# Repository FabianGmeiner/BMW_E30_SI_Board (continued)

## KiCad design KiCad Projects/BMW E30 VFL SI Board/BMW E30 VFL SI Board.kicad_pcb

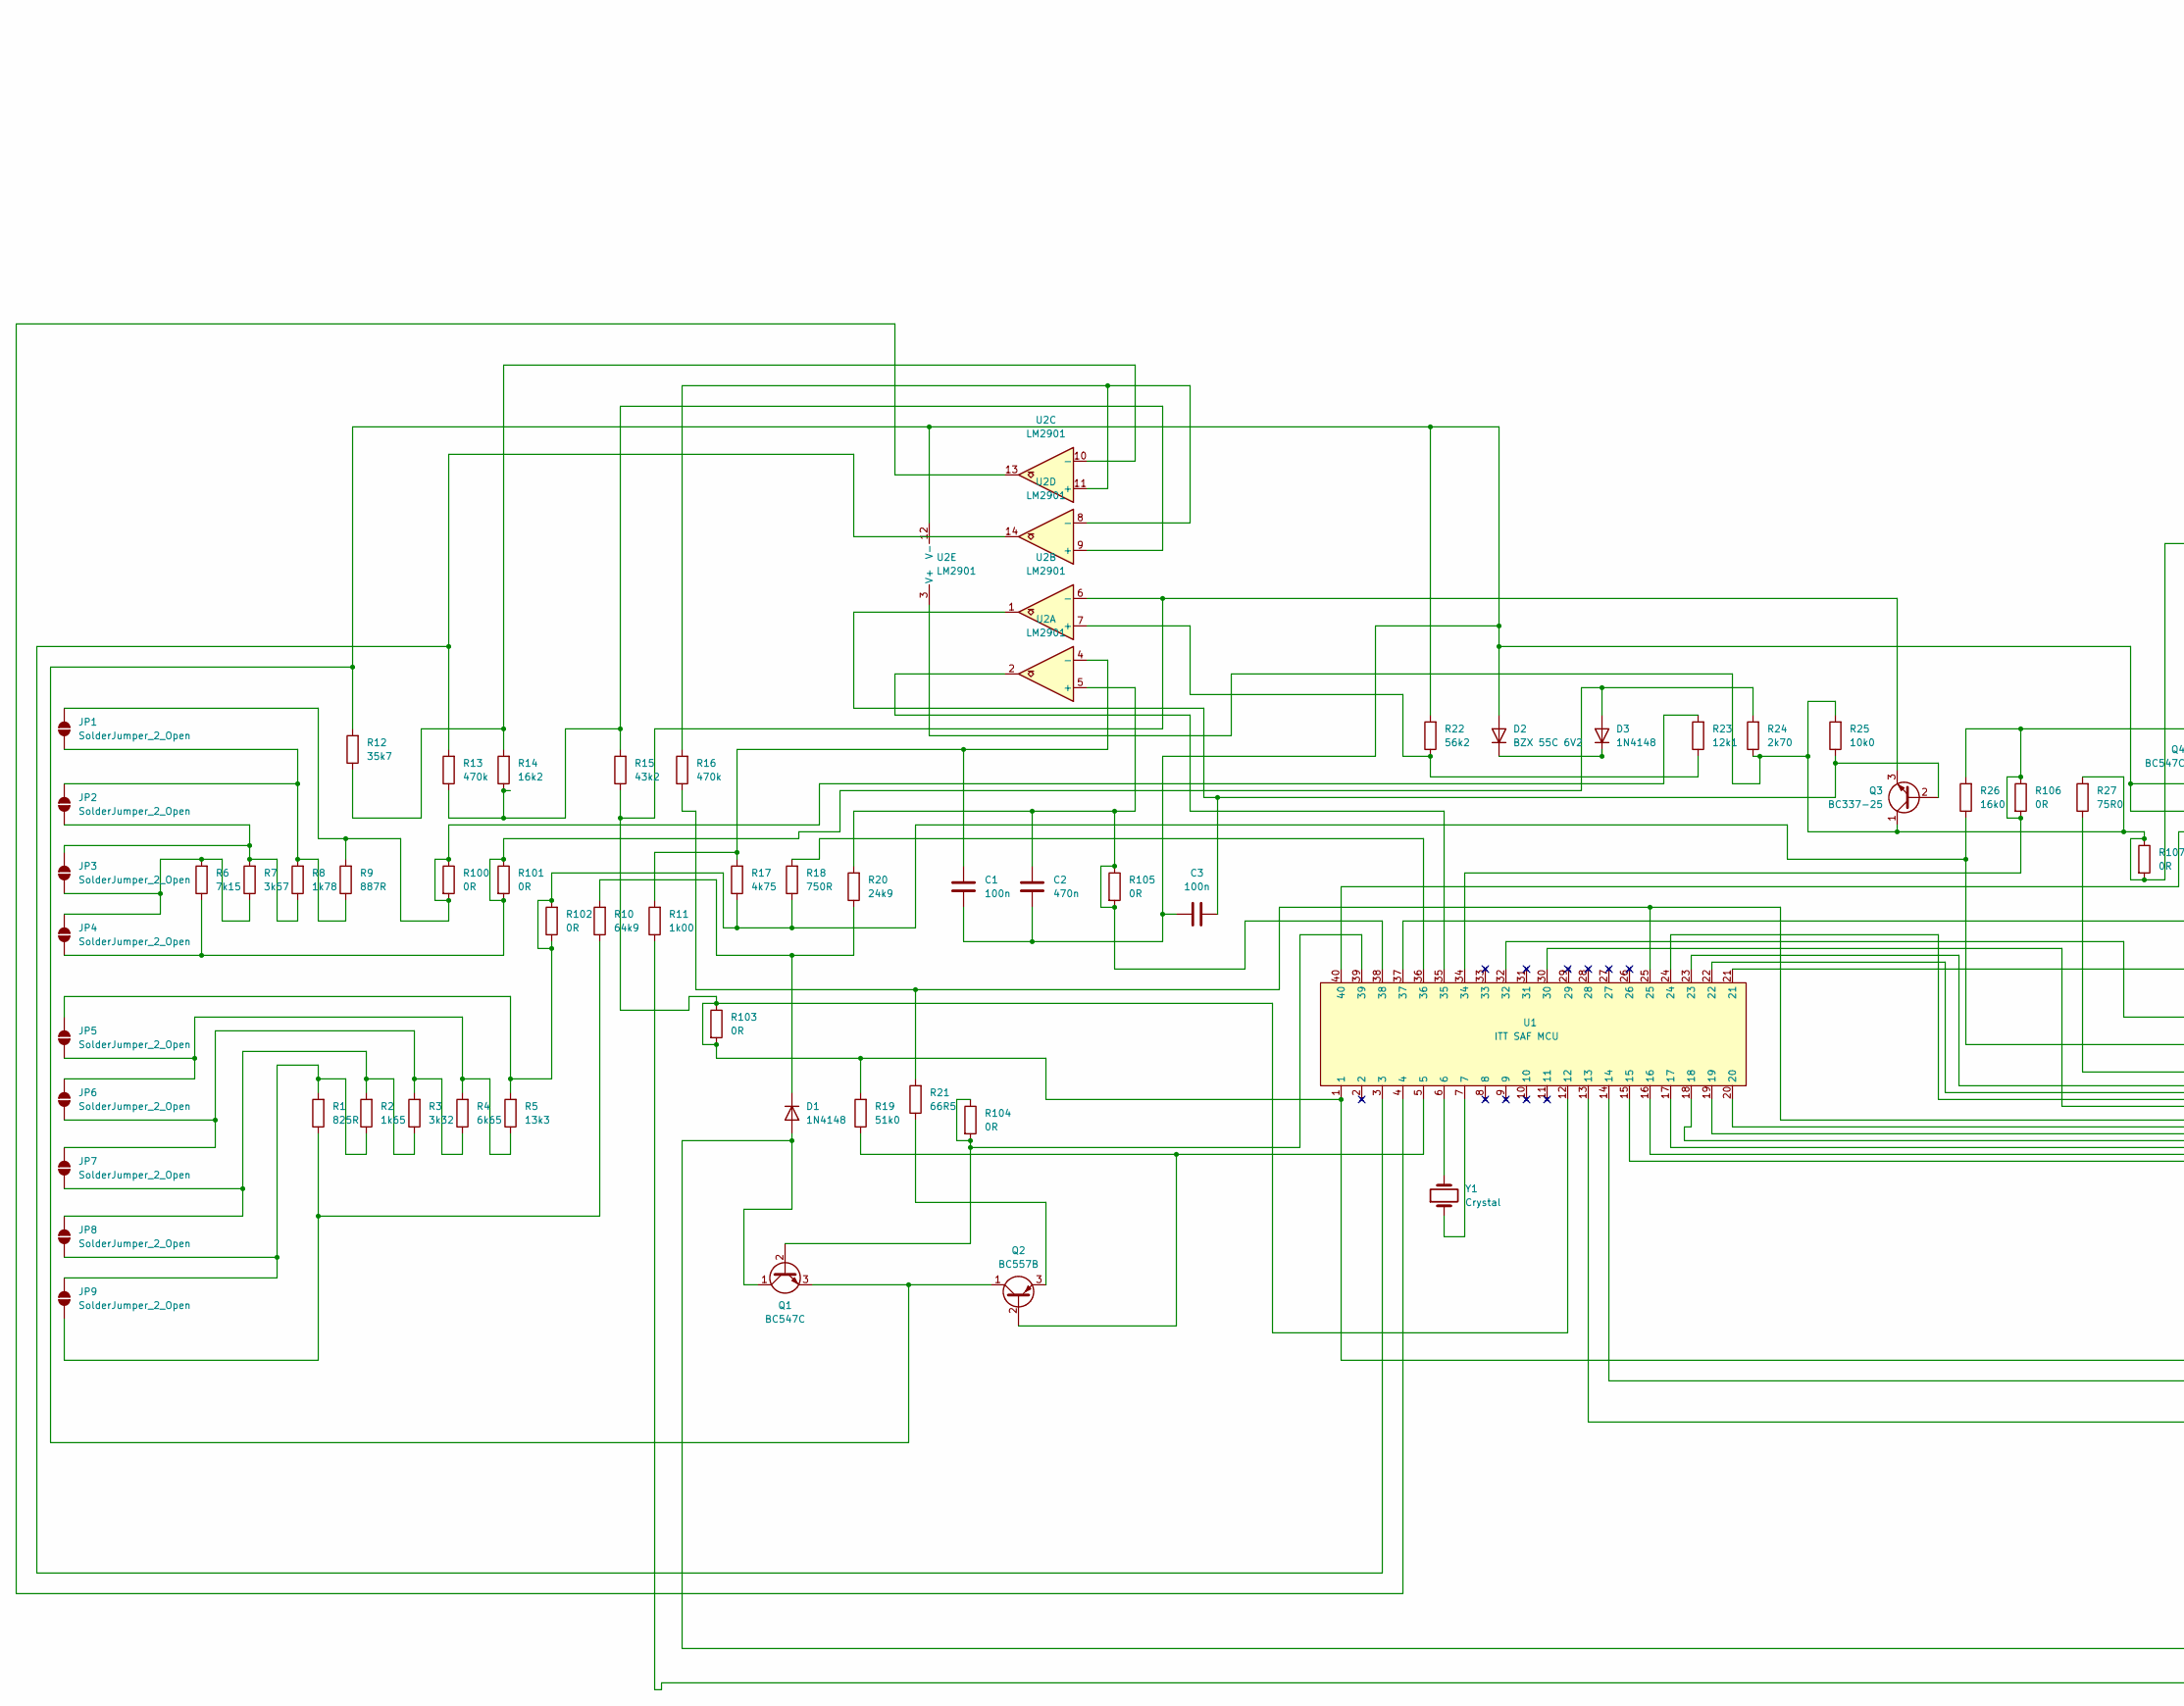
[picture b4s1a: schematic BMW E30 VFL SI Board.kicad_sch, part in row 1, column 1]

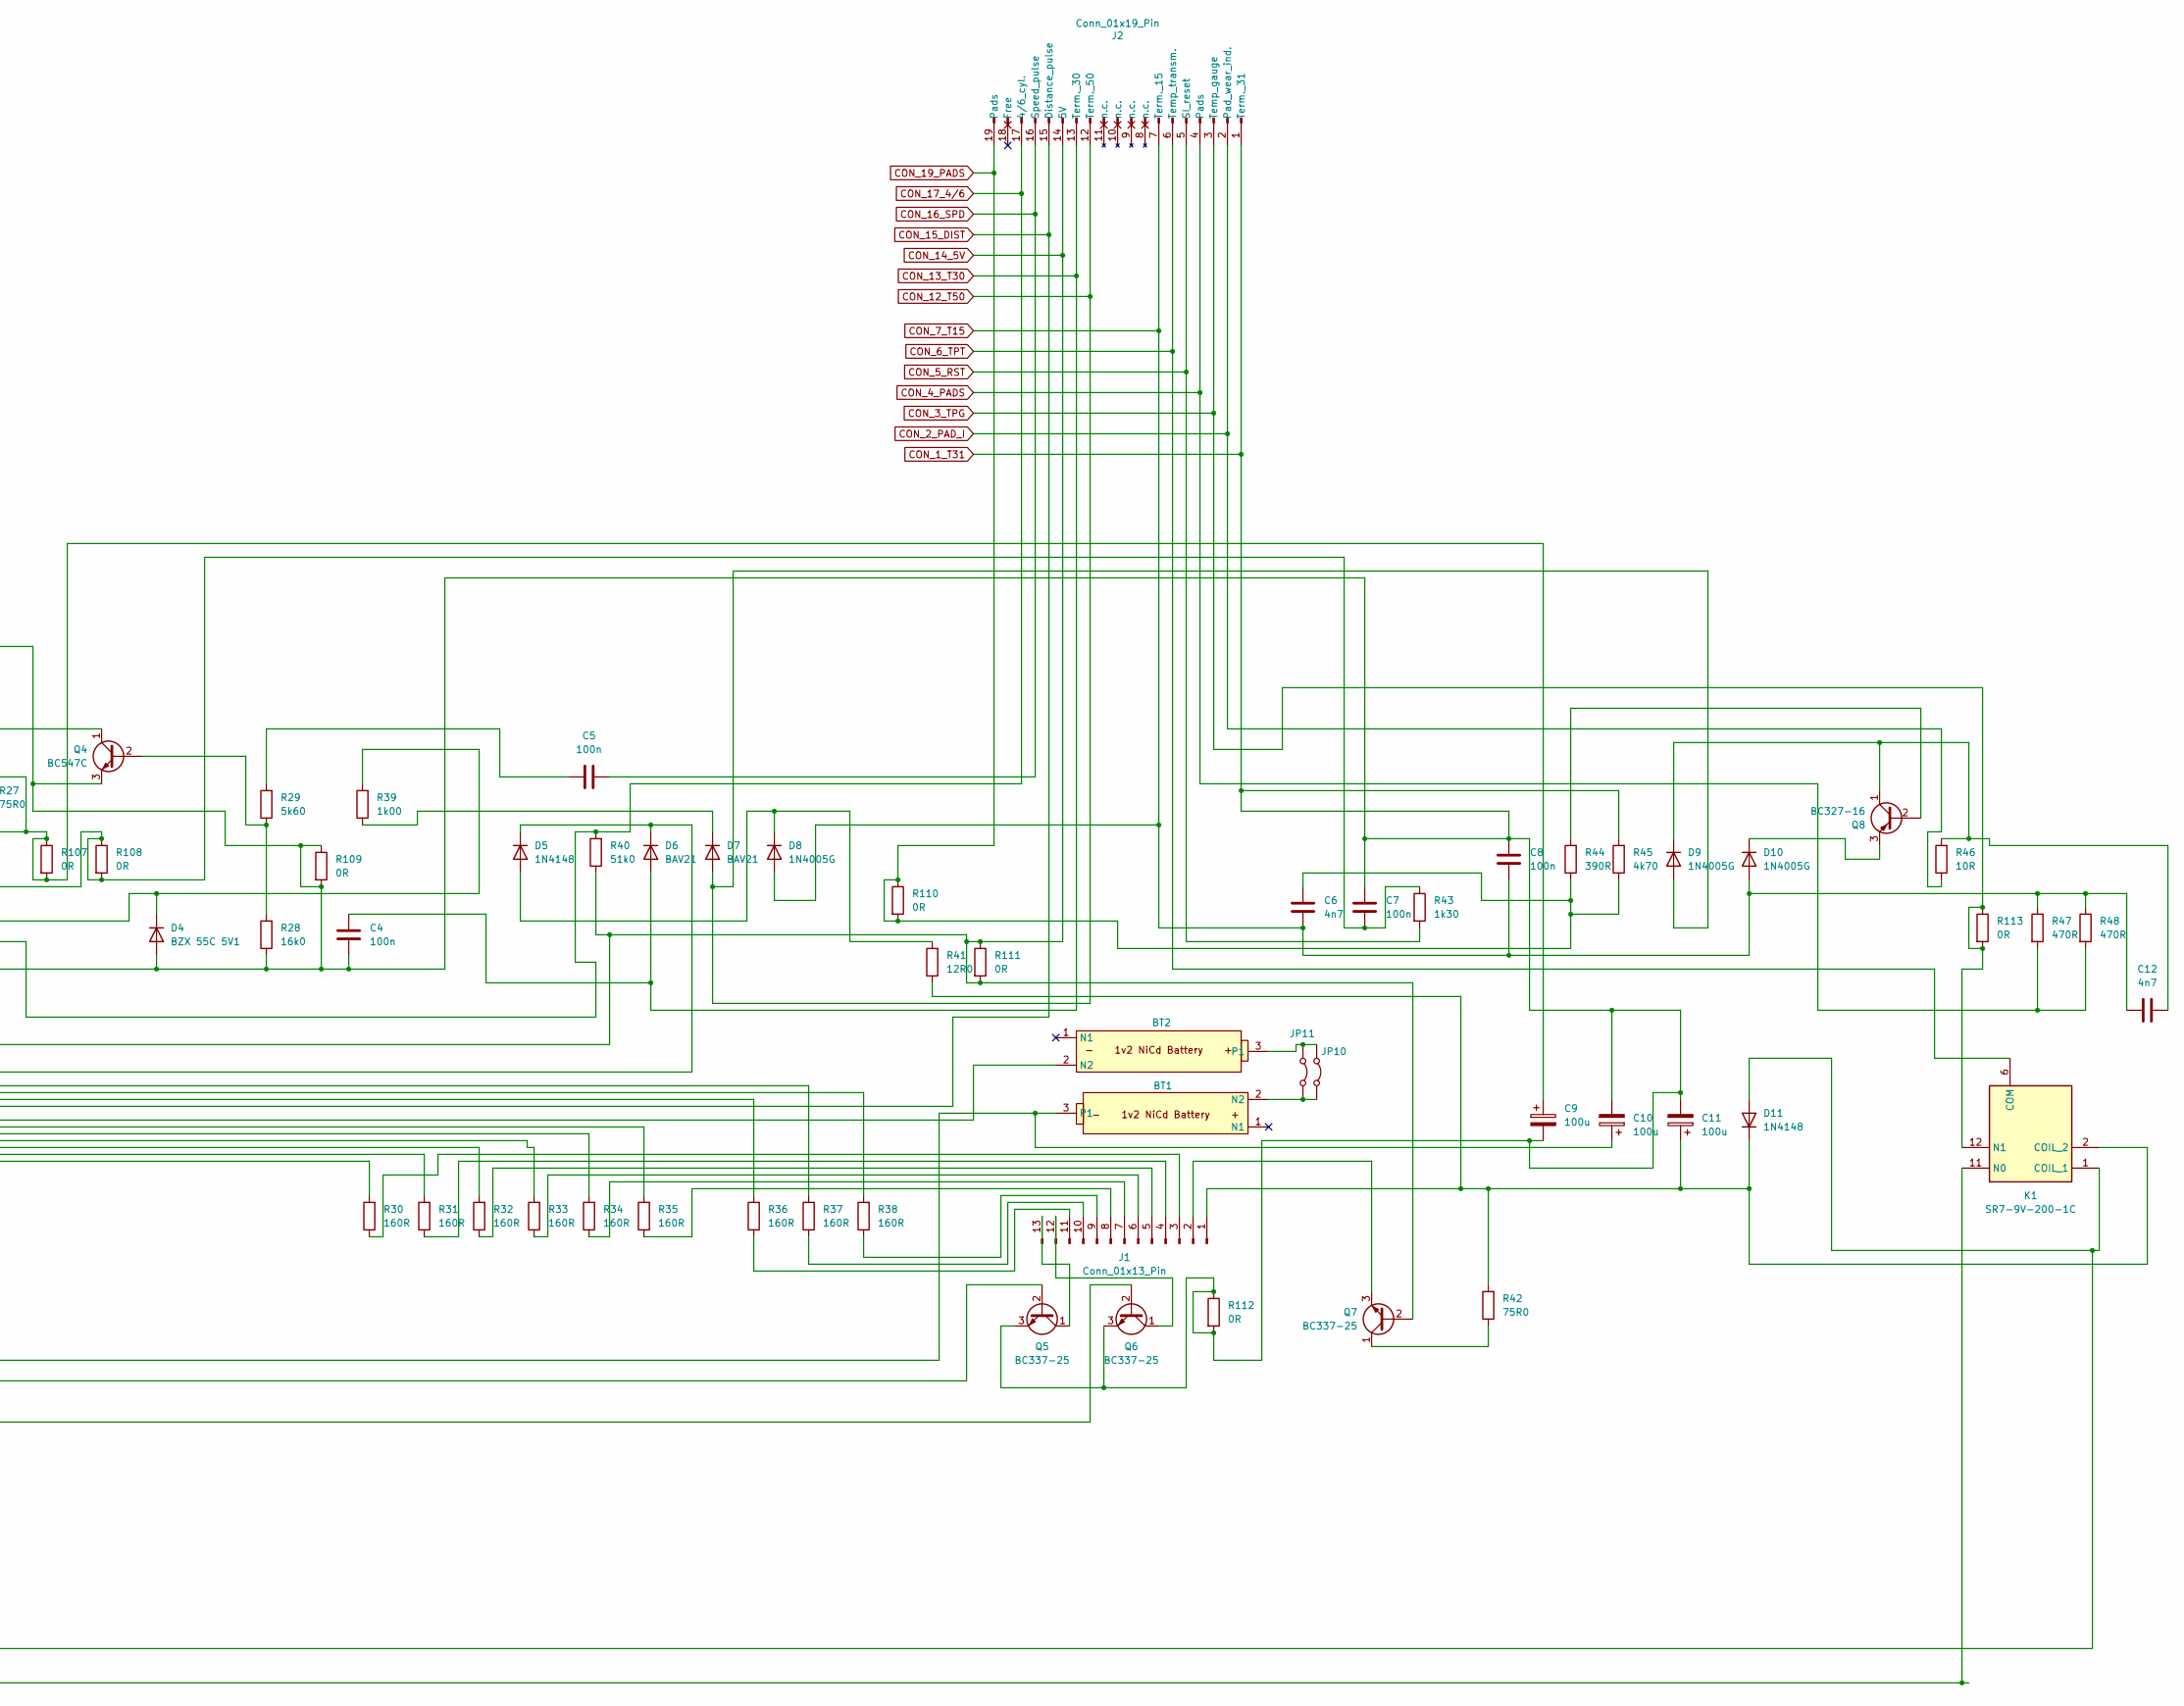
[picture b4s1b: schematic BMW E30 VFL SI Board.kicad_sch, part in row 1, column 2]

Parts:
BT1, BT2: E30 SI Battery NiCd AA
C1, C3, C4, C7, C8: 100n; C_Rect_L7.0mm_W2.5mm_P5.00mm
C2: 470n; C_Rect_L7.2mm_W5.5mm_P5.00mm_FKS2_FKP2_MKS2_MKP2
C5: 100n; C_Rect_L7.2mm_W2.5mm_P5.00mm_FKS2_FKP2_MKS2_MKP2
C6, C12: 4n7; C_Disc_D8.0mm_W2.5mm_P5.00mm
C9, C10: 100u; CP_Axial_L16.0mm_D8.5mm_P22.5mm_Horizontal
C11: 100u; CP_Axial_L18.0mm_D8.5mm_P22.5mm_Horizontal
D1, D3, D11: 1N4148; D_DO-35_SOD27_P10.16mm_Horizontal
D2: BZX 55C 6V2; D_DO-35_SOD27_P10.16mm_Horizontal
D4: BZX 55C 5V1; D_DO-35_SOD27_P10.16mm_Horizontal
D5: 1N4148; D_DO-35_SOD27_P7.62mm_Horizontal
D6: BAV21; D_DO-35_SOD27_P10.16mm_Horizontal
D7: BAV21; D_DO-35_SOD27_P12.70mm_Horizontal
D8, D9, D10: 1N4005G; D_DO-41_SOD81_P12.70mm_Horizontal
J1: Conn_01x13_Pin; PinHeader_1x13_P2.54mm_Vertical
J2: Conn_01x19_Pin; E30_SI_Connector_19Pin_P3.5
JP1, JP2, JP3, JP4, JP5, JP6, JP7, JP8, JP9: SolderJumper_2_Open; SolderJumper-2_P1.3mm_Open_Pad1.0x1.5mm
JP10: Jumper_2_Bridged; PinHeader_1x02_P2.54mm_Vertical
JP11: Jumper_2_Bridged; SolderJumper-2_P1.3mm_Open_RoundedPad1.0x1.5mm
K1: SR7-9V-200-1C; SR79V2001C; Mouser Part Number 179-SR7-9V-200-1C
Q1, Q4: BC547C; TO-92_Inline_Wide
Q2: BC557B; TO-92_Inline_Wide
Q3, Q5, Q6, Q7: BC337-25; TO-92_Inline_Wide
Q8: BC327-16; TO-92_Inline_Wide
R1: 825R; R_Axial_DIN0207_L6.3mm_D2.5mm_P10.16mm_Horizontal
R2: 1k65; R_Axial_DIN0207_L6.3mm_D2.5mm_P10.16mm_Horizontal
R3: 3k32; R_Axial_DIN0207_L6.3mm_D2.5mm_P10.16mm_Horizontal
R4: 6k65; R_Axial_DIN0207_L6.3mm_D2.5mm_P10.16mm_Horizontal
R5: 13k3; R_Axial_DIN0207_L6.3mm_D2.5mm_P10.16mm_Horizontal
R6: 7k15; R_Axial_DIN0207_L6.3mm_D2.5mm_P10.16mm_Horizontal
R7: 3k57; R_Axial_DIN0207_L6.3mm_D2.5mm_P10.16mm_Horizontal
R8: 1k78; R_Axial_DIN0207_L6.3mm_D2.5mm_P10.16mm_Horizontal
R9: 887R; R_Axial_DIN0207_L6.3mm_D2.5mm_P10.16mm_Horizontal
R10: 64k9; R_Axial_DIN0207_L6.3mm_D2.5mm_P12.70mm_Horizontal
R11: 1k00; R_Axial_DIN0207_L6.3mm_D2.5mm_P17.78mm_Horizontal
R12: 35k7; R_Axial_DIN0207_L6.3mm_D2.5mm_P10.16mm_Horizontal
R13, R16: 470k; R_Axial_DIN0207_L6.3mm_D2.5mm_P10.16mm_Horizontal
R14: 16k2; R_Axial_DIN0207_L6.3mm_D2.5mm_P10.16mm_Horizontal
R15: 43k2; R_Axial_DIN0207_L6.3mm_D2.5mm_P10.16mm_Horizontal
R17: 4k75; R_Axial_DIN0207_L6.3mm_D2.5mm_P10.16mm_Horizontal
R18: 750R; R_Axial_DIN0207_L6.3mm_D2.5mm_P12.70mm_Horizontal
R19, R40: 51k0; R_Axial_DIN0207_L6.3mm_D2.5mm_P10.16mm_Horizontal
R20: 24k9; R_Axial_DIN0207_L6.3mm_D2.5mm_P15.24mm_Horizontal
R21: 66R5; R_Axial_DIN0207_L6.3mm_D2.5mm_P10.16mm_Horizontal
R22: 56k2; R_Axial_DIN0207_L6.3mm_D2.5mm_P10.16mm_Horizontal
R23: 12k1; R_Axial_DIN0207_L6.3mm_D2.5mm_P10.16mm_Horizontal
R24: 2k70; R_Axial_DIN0207_L6.3mm_D2.5mm_P10.16mm_Horizontal
R25: 10k0; R_Axial_DIN0207_L6.3mm_D2.5mm_P10.16mm_Horizontal
R26: 16k0; R_Axial_DIN0207_L6.3mm_D2.5mm_P20.32mm_Horizontal
R27: 75R0; R_Axial_DIN0207_L6.3mm_D2.5mm_P12.70mm_Horizontal
R28: 16k0; R_Axial_DIN0207_L6.3mm_D2.5mm_P10.16mm_Horizontal
R29: 5k60; R_Axial_DIN0207_L6.3mm_D2.5mm_P10.16mm_Horizontal
R30, R31, R32, R33, R34, R35: 160R; R_Axial_DIN0207_L6.3mm_D2.5mm_P10.16mm_Horizontal
R36, R37, R38: 160R; R_Axial_DIN0207_L6.3mm_D2.5mm_P15.24mm_Horizontal
R39: 1k00; R_Axial_DIN0207_L6.3mm_D2.5mm_P12.70mm_Horizontal
R41: 12R0; R_Axial_DIN0414_L11.9mm_D4.5mm_P22.86mm_Horizontal
R42: 75R0; R_Axial_DIN0309_L9.0mm_D3.2mm_P15.24mm_Horizontal
R43: 1k30; R_Axial_DIN0207_L6.3mm_D2.5mm_P10.16mm_Horizontal
R44: 390R; R_Axial_DIN0309_L9.0mm_D3.2mm_P15.24mm_Horizontal
R45: 4k70; R_Axial_DIN0207_L6.3mm_D2.5mm_P10.16mm_Horizontal
R46: 10R; R_Axial_DIN0207_L6.3mm_D2.5mm_P10.16mm_Horizontal
R47, R48: 470R; R_Axial_DIN0309_L9.0mm_D3.2mm_P15.24mm_Horizontal
R100, R101, R106: 0R; Wire_Bridge_P15.24mm
R102, R107: 0R; Wire_Bridge_P12.70mm
R103, R108: 0R; Wire_Bridge_P10.16mm
R104: 0R; Wire_Bridge_P22.86mm
R105, R112, R113: 0R; Wire_Bridge_P7.62mm
R109, R110: 0R; Wire_Bridge_P17.78mm
R111: 0R; Wire_Bridge_P20.32mm
U1: ITT SAF MCU; DIP-40_W15.24mm
U2: LM2901; DIP-14_W7.62mm
Y1: Crystal; Crystal_C38-LF_D3.0mm_L8.0mm_Horizontal

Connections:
unnamed: BT1.2 (N2), JP10.2 (B), JP11.2 (B)
unnamed: BT1.3 (P1), C10.1, Q3.3 (E), R15.1, R19.2, R103.1, R103.2, U1.1, U1.12, U2.6 (-)
unnamed: BT2.2 (N2), R16.1, R21.2, U1.25
unnamed: BT2.3 (P1), JP10.1 (A), JP11.1 (A)
unnamed: C5.1, R29.2
unnamed: C6.1, J2.19 (Pads), R44.1, R45.1, R110.1, R110.2
unnamed: C7.1, R43.1, R108.1, R108.2, U1.40
unnamed: D1.2 (A), D11.2 (A), K1.1 (COIL_1), Q1.1 (C)
unnamed: D1.1 (K), R10.2, R20.1
unnamed: C1.1, C2.1, C3.1, C4.1, C7.2, C8.1, C9.2, C10.2, C11.2, D2.2 (A), D4.2 (A), J2.1 (Term._31), Q1.3 (E), Q2.1 (C), Q4.3 (E), Q5.3 (E), Q6.3 (E), R12.2, R22.2, R28.1, R45.2, R109.1, R109.2, R112.1, R112.2, U1.21, U2.12 (V-)
unnamed: D2.1 (K), D3.1 (K)
unnamed: D3.2 (A), JP4.2 (B), R6.1, R24.2, R101.1, R101.2
unnamed: D4.1 (K), R39.2, U1.37
unnamed: D5.2 (A), D8.1 (K), R41.2
unnamed: D5.1 (K), D6.1 (K), R27.1
unnamed: C4.2, D6.2 (A), J2.13 (Term._30)
unnamed: D7.2 (A), D9.2 (A), J2.12 (Term._50)
unnamed: D7.1 (K), R39.1
unnamed: C12.2, D9.1 (K), Q8.1 (C), R46.2
unnamed: C6.2, C8.2, C12.1, D8.2 (A), D10.2 (A), J2.7 (Term._15), R47.1, R48.1
unnamed: D10.1 (K), Q8.3 (E)
unnamed: C11.1, D11.1 (K), J1.1 (GND_BULB), K1.2 (COIL_2), R41.1, R42.2
unnamed: J1.12 (BULB_INSPECTION), Q6.1 (C)
unnamed: J1.13 (BULB_OILSERVICE), Q5.1 (C)
unnamed: J1.2 (GND_LED), Q7.3 (E)
unnamed: J1.11 (LED_G1), R36.1
unnamed: J1.10 (LED_G2), R37.1
unnamed: J1.9 (LED_G3), R38.1
unnamed: J1.8 (LED_G4), R35.1
unnamed: J1.7 (LED_G5), R34.1
unnamed: J1.5 (LED_R1), R32.1
unnamed: J1.4 (LED_R2), R31.1
unnamed: J1.3 (LED_R3), R30.1
unnamed: J1.6 (LED_Y), R33.1
unnamed: J2.17 (4/6_cyl.), R40.2, U1.32
unnamed: J2.14 (5V), JP5.1 (A), Q7.2 (B), R5.2, R17.1, R18.1, R26.1, R40.1, R102.1, R102.2, R111.1, R111.2
unnamed: J2.15 (Distance_pulse), U1.30
unnamed: J2.2 (Pad_wear_ind.), R46.1
unnamed: J2.4 (Pads), R47.2, R48.2
unnamed: J2.5 (SI_reset), R43.2
unnamed: C5.2, J2.16 (Speed_pulse)
unnamed: J2.3 (Temp_gauge), K1.12 (N1), R113.1, R113.2
unnamed: J2.6 (Temp_transm.), K1.6 (COM)
unnamed: JP1.1 (A), R9.2, R23.2, R100.1, R100.2
unnamed: JP1.2 (B), JP2.1 (A), R8.2, R9.1
unnamed: JP2.2 (B), JP3.1 (A), R7.2, R8.1
unnamed: JP3.2 (B), JP4.1 (A), R6.2, R7.1
unnamed: JP5.2 (B), JP6.1 (A), R4.2, R5.1
unnamed: JP6.2 (B), JP7.1 (A), R3.2, R4.1
unnamed: JP7.2 (B), JP8.1 (A), R2.2, R3.1
unnamed: JP8.2 (B), JP9.1 (A), R1.2, R2.1
unnamed: JP9.2 (B), R1.1, R10.1
unnamed: K1.11 (N0), R11.1
unnamed: Q1.2 (B), R104.1, R104.2, U1.39
unnamed: Q2.2 (B), R19.1, U1.5
unnamed: Q2.3 (E), R21.1
unnamed: C3.2, Q3.2 (B), R25.1, U2.1
unnamed: C9.1, Q3.1 (C), R24.1, R25.2, R27.2, R107.1, R107.2, U2.3 (V+)
unnamed: Q4.2 (B), R28.2, R29.1
unnamed: Q4.1 (C), R26.2, R106.1, R106.2, U1.34
unnamed: Q5.2 (B), U1.14
unnamed: Q6.2 (B), U1.13
unnamed: Q7.1 (C), R42.1
unnamed: Q8.2 (B), R44.2
unnamed: R13.2, U1.3, U2.14
unnamed: R18.2, U1.36
unnamed: R30.2, U1.15
unnamed: R31.2, U1.16
unnamed: R32.2, U1.17
unnamed: R33.2, U1.18
unnamed: R34.2, U1.19
unnamed: R35.2, U1.20
unnamed: R36.2, U1.24
unnamed: R37.2, U1.23
unnamed: R38.2, U1.22
unnamed: U1.4, U2.13
unnamed: U1.6, Y1.2
unnamed: U1.7, Y1.1
unnamed: U1.35, U2.2
unnamed: C2.2, R20.2, R105.1, R105.2, U1.38, U2.5 (+)
unnamed: C1.2, R11.2, R17.2, U2.4 (-)
unnamed: R22.1, R23.1, U2.7 (+)
unnamed: R16.2, U2.8 (-), U2.11 (+)
unnamed: R12.1, R14.2, U2.10 (-)
unnamed: R13.1, R14.1, R15.2, U2.9 (+)

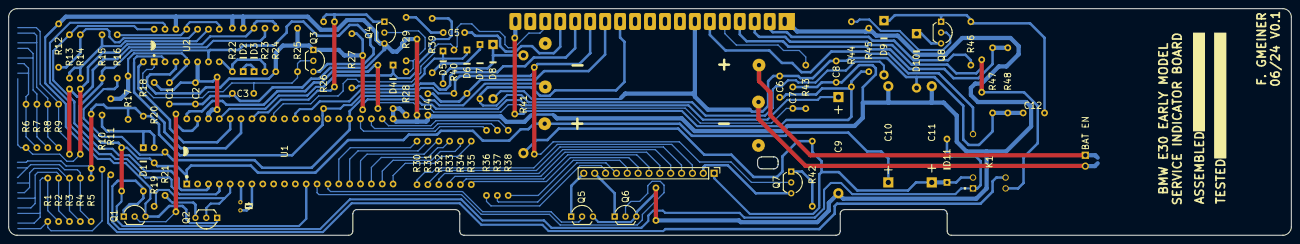
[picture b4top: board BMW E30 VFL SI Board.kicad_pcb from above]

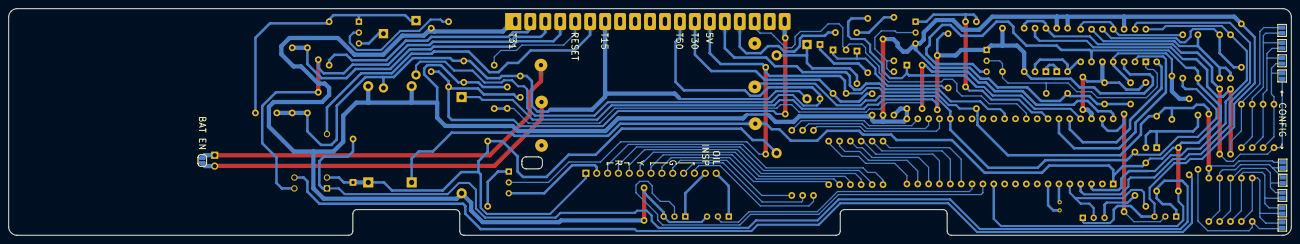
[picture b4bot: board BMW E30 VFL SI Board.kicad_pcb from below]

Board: 2 copper layers, 300.0 x 53.0 mm, 112 parts (10 on the bottom side), 85 nets.

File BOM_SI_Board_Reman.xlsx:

|  |  | BMW E30 VVFL Si-Board VDO Bill of Materials
 |  |  |  |  |  |  |  |  |  | SUMME Mouser |  |  | SUMME Reichelt
 |  |  |  |  |  |  |  |  |  | 6.4660000000000002 |  |  | 4.0549999999999988
 | Sum of Qty: | 102
Item # | *Designator | *Qty | Manufacturer | Qty. for 10 boards | Description / Value | *Package/Footprint | Type | Your Instructions / Notes | Mouser Nr. | Mouser Unit Price | Mouser Total Price | Reichelt Nr. | Reichelt Unit Price | Reichelt Total Price
1 | R1 | 1 |  | 10 | 825 Ohms 2% 1/4W | THT |  |  |  |  |  | METALL 825 | 3.5000000000000003E-2 | 3.5000000000000003E-2
2 | R2 | 1 |  | 10 | 1.65k Ohms 1% 1/4W | THT |  |  |  |  |  | METALL 1,65K | 3.5000000000000003E-2 | 3.5000000000000003E-2
3 | R3 | 1 |  | 10 | 3.32k Ohms 2% 50ppm 1/4W | THT |  |  |  |  |  | METALL 3,32K | 3.5000000000000003E-2 | 3.5000000000000003E-2
4 | R4 | 1 |  | 10 | 6.65k Ohms 1% 1/4W | THT |  |  |  |  |  | METALL 6,65K | 3.5000000000000003E-2 | 3.5000000000000003E-2
5 | R5 | 1 |  | 10 | 13.3k Ohms 2% 1/4W | THT |  |  |  |  |  | METALL 13,3K | 3.5000000000000003E-2 | 3.5000000000000003E-2
6 | R6 | 1 |  | 10 | 7.15k Ohms 2% 1/4W | THT |  |  |  |  |  | METALL 7,15K | 3.5000000000000003E-2 | 3.5000000000000003E-2
7 | R7 | 1 |  | 10 | 3.57k Ohms 1% 1/4W | THT |  |  |  |  |  | METALL 3,57K | 0.06 | 0.06
8 | R8 | 1 |  | 10 | 1.78k Ohms 1% 1/4W | THT |  |  |  |  |  | METALL 1,78K | 3.5000000000000003E-2 | 3.5000000000000003E-2
9 | R9 | 1 |  | 10 | 887 Ohms 1% 1/4W | THT |  |  |  |  |  | METALL 887 | 3.5000000000000003E-2 | 3.5000000000000003E-2
10 | R10 | 1 |  | 10 | 64.9k Ohms 2% 1/4W | THT |  |  |  |  |  | METALL 64,9K | 3.5000000000000003E-2 | 3.5000000000000003E-2
11 | R11, R39 | 2 |  | 10 | 1k Ohms 2% 1/4W | THT |  |  |  |  |  | METALL 1,00K | 3.5000000000000003E-2 | 7.0000000000000007E-2
12 | R12 | 1 |  | 10 | 35.7k Ohms 1% 1/4W | THT |  |  |  |  |  | METALL 35,7K | 0.05 | 0.05
13 | R13, R16 | 2 |  | 10 | 470k Ohms 5% 1/4W | THT |  |  |  |  |  | METALL 470K | 3.5000000000000003E-2 | 7.0000000000000007E-2
14 | R14 | 1 |  | 10 | 16.2k Ohms 2% 1/4W | THT |  |  |  |  |  | METALL 16,2K | 3.5000000000000003E-2 | 3.5000000000000003E-2
15 | R15 | 1 |  | 10 | 43.2k Ohms 1% 1/4W | THT |  |  |  |  |  | METALL 43,2K | 3.5000000000000003E-2 | 3.5000000000000003E-2
16 | R17 | 1 |  | 10 | 4.75k Ohms 2% 50ppm 1/4W | THT |  |  |  |  |  | METALL 4,75K | 3.5000000000000003E-2 | 3.5000000000000003E-2
17 | R18 | 1 |  | 10 | 750 Ohms 5% 1/2W | THT |  |  | MF1/2CCT52R7500F | 0.40600000000000003 | 0.40600000000000003
18 | R19, R40 | 2 |  | 10 | 51k Ohms 5% 1/4W | THT |  |  |  |  |  | METALL 51,0K | 3.5000000000000003E-2 | 7.0000000000000007E-2
19 | R20 | 1 |  | 10 | 24.9k Ohms 2% 1/4W | THT |  |  |  |  |  | METALL 24,9K | 3.5000000000000003E-2 | 3.5000000000000003E-2
20 | R21 | 1 |  | 10 | 66.5 Ohms 1% 1/4W | THT |  |  |  |  |  | METALL 66,5 | 0.08 | 0.08
21 | R22 | 1 |  | 10 | 56.2k Ohms 2% 1/4W | THT |  |  |  |  |  | METALL 56,2K | 3.5000000000000003E-2 | 3.5000000000000003E-2
22 | R23 | 1 |  | 10 | 12.1k Ohms 1% 1/4W | THT |  |  |  |  |  | METALL 12,1K | 3.5000000000000003E-2 | 3.5000000000000003E-2
23 | R24 | 1 |  | 10 | 2.7k Ohms 5% 1/4W | THT |  |  |  |  |  | METALL 2,70K | 3.5000000000000003E-2 | 3.5000000000000003E-2
24 | R25 | 1 |  | 10 | 10k Ohms 5% 1/4W | THT |  |  |  |  |  | METALL 10,0K | 3.5000000000000003E-2 | 3.5000000000000003E-2
25 | R26, R28 | 2 |  | 10 | 16k Ohms 5% 1/4W | THT |  |  |  |  |  | METALL 16,0K | 3.5000000000000003E-2 | 7.0000000000000007E-2
26 | R27 | 1 |  | 10 | 75 Ohms 10% 1/4W | THT |  |  |  |  |  | METALL 75,0 | 3.5000000000000003E-2 | 3.5000000000000003E-2
27 | R29 | 1 |  | 10 | 5.6k Ohms 5% 1/4W | THT |  |  |  |  |  | METALL 5,60K | 3.5000000000000003E-2 | 3.5000000000000003E-2
28 | R30 - R38 | 9 |  | 45 | 160 Ohms 5% 1/4W | THT |  |  |  |  |  | METALL 160 | 3.5000000000000003E-2 | 0.31500000000000006
29 | R41 | 1 |  | 10 | 12 Ohms 2% 1W | THT |  |  |  |  |  | VI MBE04140C1209 | 0.17 | 0.17
30 | R42 | 1 |  | 10 | 75 Ohms 5% 1/2W | THT |  |  | MF1/2DCT52R75R0F | 0.39200000000000002 | 0.39200000000000002
31 | R43 | 1 |  | 10 | 1.3k Ohms 5% 1/4W | THT |  |  |  |  |  | METALL 1,30K | 3.5000000000000003E-2 | 3.5000000000000003E-2
32 | R44 | 1 |  | 10 | 390 Ohms 5% 1/2W | THT |  |  | MF1/2DCT52R3900F | 0.39200000000000002 | 0.39200000000000002
33 | R45 | 1 |  | 10 | 4.7k Ohms 5% 1/4W | THT |  |  |  |  |  | METALL 4,70K | 3.5000000000000003E-2 | 3.5000000000000003E-2
34 | R46 | 1 |  | 10 | 10 Ohms 5% 1/4W | THT |  |  |  |  |  | METALL 10,0 | 3.5000000000000003E-2 | 3.5000000000000003E-2
35 | R47, R48 | 2 |  | 10 | 470 Ohms 5% 1/2W | THT |  |  | MF1/2DCT52R4700F | 0.22900000000000001 | 0.45800000000000002
36 | R100 - R113 | 13 |  | 130 | 0 Ohm wire bridge | THT |  | DNP
37 | D1, D3, D5, D11 | 4 | Vishay, onsemi | 20 | 1N4148 | DO-35 |  |  | 512-1N4148 | 5.2999999999999999E-2 | 0.21199999999999999
38 | D2 | 1 | Vishay, onsemi, Taiwan Semiconductor | 10 | BZX 55C 6V2 500mW | DO-35 |  |  | 78-BZX55C6V2-TAP | 0.10100000000000001 | 0.10100000000000001
39 | D4 | 1 | Vishay, onsemi, Taiwan Semiconductor | 10 | BZX 55C 5V1 500mW | DO-35 |  |  | 78-BZX55C5V1 | 0.10199999999999999 | 0.10199999999999999
40 | D6, D7 | 2 | Vishay, onsemi, Taiwan Semiconductor, Diotec | 10 | BAV21 250mW | DO-35 |  |  |  |  |  | BAV 21 | 0.04 | 0.08
41 | D8, D9, D10 | 3 | onsemi, Teiwan Semiconductor | 15 | 1N4005G | DO-41 |  |  | 863-1N4005RLG | 7.2999999999999995E-2 | 0.21899999999999997
42 | C1, C3, C4, C7, C8 | 5 | KEMET, Vishay, AVX | 25 | 100nF +50/-20% >=63V | THT, LS=5.08mm | Ceramic MLCC |  | 81-RCER72A104K1M1H3A | 0.17899999999999999 | 0.89500000000000002
43 | C2 | 1 | Vishay | 5 | 470nF 10% 63V MKT1817 | THT, LS=5.08mm | Film |  | MKT1817447065 | 0.755 | 0.755
44 | C5 | 1 | Vishay | 5 | 100nF 20% 63V MKT1817 | THT, LS=5.08mm | Film |  | MKT1817410065 | 0.42899999999999999 | 0.42899999999999999
45 | C6, C12 | 2 | Murata, KEMET | 10 | 4,7nF 10% 1000V | THT, LS=5 / 5.08mm | Ceramic MLCC | RDER73A473K4M1H03A |  |  |  | KERKO-500 4,7N | 0.05 | 0.1
46 | C9, C10 | 2 | Vishay, Cornell | 10 | 100µF 20% 16V 85°C | Axial, D < 8,5mm, L< 18mm | Elco | MAL213825101E3 |  |  |  | AX 105 100/16 | 0.43 | 0.86
47 | C11 | 1 | Vishay | 5 | 100µF 20% 63V 85°C | Axial, D < 8,5mm, L< 18mm | Elco | MAL202138101E3 |  |  |  | COS 105 100/63 | 0.49 | 0.49
48 | Q1, Q4 | 2 | Diotec, onsemi | 10 | BC547C 100mA 45V | TO-92 Kinked Lead |  | original: BC237C obsolete |  |  |  | BC 547C | 0.05 | 0.1
49 | Q2 | 1 | Diotec, onsemi | 10 | BC557B 100mA 45V | TO-92 Kinked Lead |  | original: BC307B obsolete |  |  |  | BC 557B | 0.05 | 0.05
50 | Q3, Q5, Q6, Q7 | 4 | onsemi | 20 | BC337-25 800mA 45V | TO-92 Kinked Lead |  |  |  |  |  | BC 337-25 | 0.06 | 0.24
51 | Q8 | 1 | onsemi | 10 | BC327-16 800mA 45V | TO-92 Kinked Lead |  |  |  |  |  | BC 327-16 | 0.06 | 0.06
52 | K1 | 1 | CUI | 10 | SR7-9V-200-1C | THT |  | original: MZ-9HS-C, alternative HKE HRS1KH-S-DC9V, TE OUAZ-SS-109L,900 | 179-SR7-9V-200-1C | 1.01 | 1.01
53 | Y1 | 1 |  | 10 |  |  |  | no markings |  |  | 0
54 | U1 | 1 | ITT | 10 | TE 1-2199299-5 or Amphenol DILB40P-223TLF | DIP-40 |  | take over from original PCB | 571-1-2199299-5 | 0.64500000000000002 | 0.64500000000000002
55 | U2 | 1 | Texas Instruments | 10 | LM2901N | PDIP-14 |  |  | 595-LM2901N | 0.45 | 0.45
56 | BT1, BT2 | 2 | Varta Ni-Cd 500 RST, 780mAh | 20 | NiCd Batteries |  |  | https://www.timsclassicparts.nl/de_DE/a-63630636/tacho-zahnr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
57 | J1 | 1 | BMW | 10 | 19 Pin 3mm Pitch Molded Frame 90° |  |  | take over from original PCB
58 | J2 | 1 | Molex 22-28-4130, Würth 61301311121 | 10 | 13 Pin standard 2,54mm pitch pin header |  |  |  |  |  |  | SL 1X40G 2,54 | 0.27 | 0.27
59 | J3 | 1 |  | 10 | 2 Pin standard 2,54 pitch pin header |  |  |  |  |  |  | MPE 087-1-002 | 0.06 | 0.06
60 | J4 | 1 |  | 10 | 2 pin standard 2,54 pitch jumper |  |  |  |  |  |  | JUMPER 2,54 SW | 0.02 | 0.02

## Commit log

2024-06-16 Rename IMG20240504111010.jpg to Traces_High_Res.jpg
2024-06-17 Bugfixing of component designators
2024-06-19 Added License
2024-06-19 Create LICENSE
2024-06-19 Added LED board schematics with LEDs instead of Bulbs
2024-06-19 Bundle schematics in folder
2024-06-24 Moved connectur up 2.5mm to correct board fitment
2024-06-24 Moved connector up 2.5mm to correct board fitment
2024-06-24 Facelift version inficator board, 7 LEDs (1 Red)
2024-06-24 Added step files to 3d print the LED holders
    Tested with JLCPCBs resin printing standard "LEDO" resin, fitment is perfect
2024-06-24 Updated assembly status
2024-06-24 Assembly images
2024-06-26 Updated Info on Reset and Coding Interface
2024-06-30 Updated testing status
2024-07-02 Updated testing report for battery charging
2024-07-13 Updated Resistor Values from 160 to 510 Ohm
2024-07-13 Updated resistor values
2024-07-13 Added BOM for Indicator Boards
2024-07-18 Added V3 with update to CR123 Lithium Battery
    Copy of the addon circuit that BMW used in the later boards and the "converted" boards with the little addon PCB. Uses a single CR123 3V lithium battery. This has a capacity of ~1600mAh compared to t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
2024-07-18 Updated for Lithium-Battery V3
2024-08-18 Printable bending guide for resistors and diodes
2024-08-18 Added Mouser Part Nrs + Bending Pitch
2024-08-23 Increase mounting hole diameter to 6.5mm
